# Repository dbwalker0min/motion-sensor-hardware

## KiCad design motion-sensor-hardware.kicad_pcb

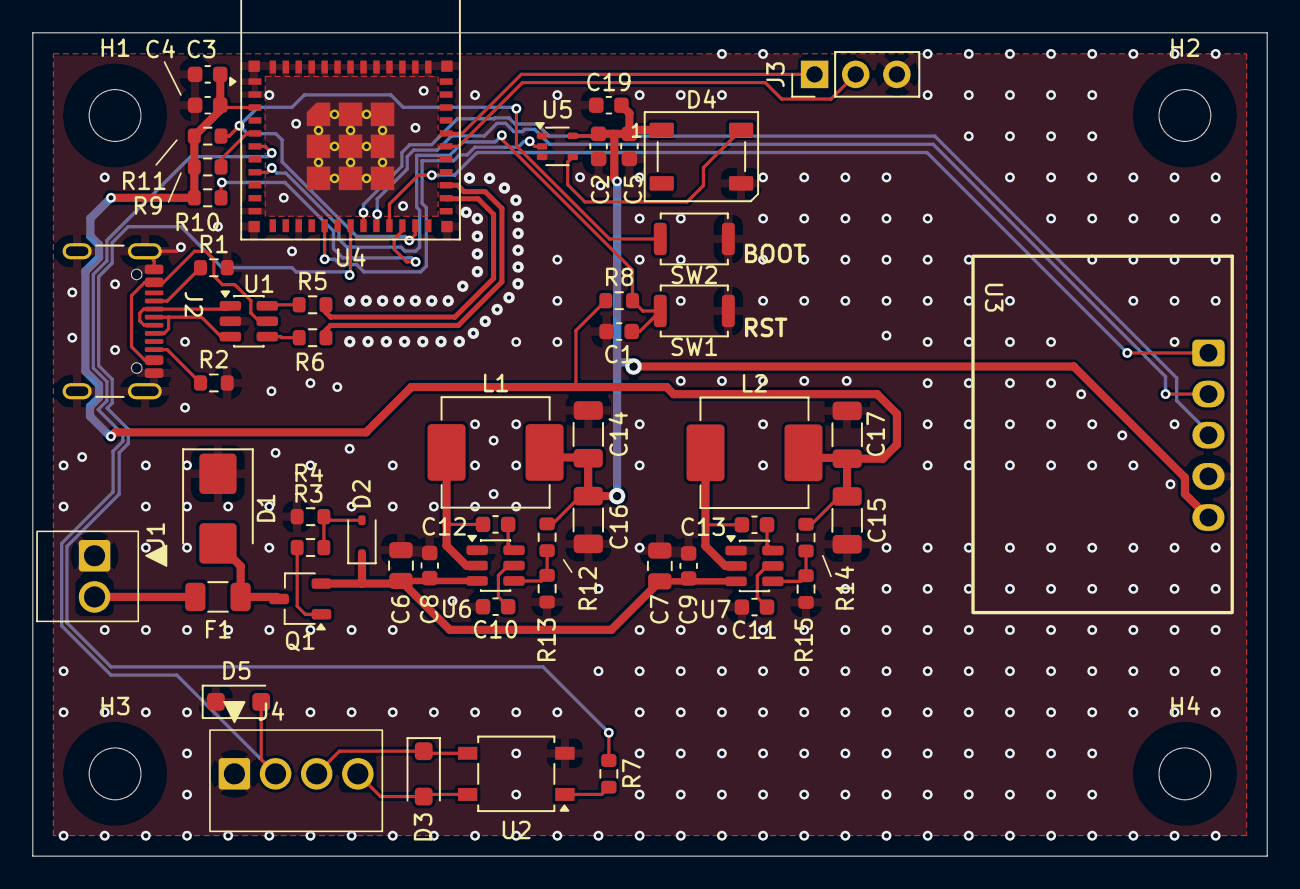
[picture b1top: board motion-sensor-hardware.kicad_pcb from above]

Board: 2 copper layers, 76.2 x 50.8 mm, 59 parts (0 on the bottom side), 41 nets.

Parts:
C1: 1uF; C_0603_1608Metric
C2, C3, C5, C8, C9, C10, C11, C12, C13: 100nF; C_0603_1608Metric
C4, C19: 10uF; C_0603_1608Metric
C6, C7: 10uF; C_0805_2012Metric
C14, C15, C16, C17: 47uF; C_1206_3216Metric
D1: SMBJ16CA; D_SMB
D2: BZT52C10S; D_SOD-323
D3, D5: SMF6.5CA; D_SOD-123F
D4: WS2812B-HS01/W; LED_WS2812B_PLCC4_5.0x5.0mm_P3.2mm
F1: JK-nSMD100/16V; Fuse_1206_3216Metric
H1, H2, H3, H4: MountingHole; MountingHole_3.2mm_M3
J1: MX128-2.54-02P
J2: TYPE-C 16PIN 2MD(073); USB_C_Receptacle_GCT_USB4105-xx-A_16P_TopMnt_Horizontal
J3: PZ254V-11-03P; PinHeader_1x03_P2.54mm_Vertical
J4: MX128-2.54-04P
L1, L2: FXL0630-6R8-M; L_Changjiang_FXL0630
Q1: AO3401A; TSOT-23
R1, R2: 5.1kΩ; R_0603_1608Metric
R3: 100Ω; R_0603_1608Metric
R4, R8, R9, R10, R11: 10kΩ; R_0603_1608Metric
R5, R6: 0Ω; R_0603_1608Metric
R7: 330Ω; R_0603_1608Metric
R12: 20kΩ; R_0603_1608Metric
R13: 3.6kΩ; R_0603_1608Metric
R14: 49.9kΩ; R_0603_1608Metric
R15: 15kΩ; R_0603_1608Metric
SW1, SW2: TS-1088-AR02016; SW_TS-1088-xx020xx_XUNPU
U1: USBLC6-2SC6; SOT-23-6
U2: ASSR-1218; SO-4_4.4x4.3mm_P2.54mm
U3: LD2410C
U4: ESP32-C3-MINI-1-N4; ESP32-C6-MINI-1
U5: SN74LV1T125DCK; SOT-353_SC-70-5
U6, U7: AP62200TWU-7; SOT-23-6

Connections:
+3.3V: C3.1, C4.1, C15.1, C17.1, L2.2, R8.1, R9.1, R10.1, R11.1, R14.1, U4.3 (3V3)
+5V: C2.1, C5.1, C14.1, C16.1, C19.1, D4.1 (VDD), L1.2, R12.1, U3.5 (VCC), U5.5 (VCC)
/CTL_SW1: D3.2 (A2), J4.4, U2.4
/CTL_SW2: D3.1 (A1), J4.3, U2.3
/LED: U4.16 (GPIO10), U5.2 (A)
/OUT: U3.3 (OUT), U4.19 (GPIO5/ADC2_CH0)
/RDR_RX: U3.2 (RX), U4.20 (GPIO6)
/RDR_TX: U3.1 (TX), U4.21 (GPIO7)
/STAT_SW: D5.2 (A2), J4.2, U4.6 (GPIO3/ADC1_CH3)
/SWON: R7.1, U4.18 (GPIO4/ADC1_CH4)
/UART_RXD: J3.2, U4.30 (GPIO20/U0RXD)
/UART_TXD: J3.1, U4.31 (GPIO21/U0TXD)
/USB+: R6.2, U4.27 (GPIO19/USB_D+)
/USB-: R5.2, U4.26 (GPIO18/USB_D-)
/VRAW: F1.1, J1.2
GND: C1.2, C2.2, C3.2, C4.2, C5.2, C6.2, C7.2, C8.2, C9.2, C10.2, C11.2, C14.2, C15.2, C16.2, C17.2, C19.2, D1.1 (A1), D4.3 (VSS), D5.1 (A1), J1.1, J2.A1 (GND), J2.A12 (GND), J2.B1 (GND), J2.B12 (GND), J2.S1 (SHIELD), J3.3, J4.1, R1.2, R2.2, R4.2, R13.2, R15.2, SW1.1, SW2.1, U1.2 (GND), U2.2, U3.4 (GND), U4.1 (GND), U4.2 (GND), U4.11 (GND), U4.14 (GND), U4.36 (GND), U4.37 (GND), U4.38 (GND), U4.39 (GND), U4.40 (GND), U4.41 (GND), U4.42 (GND), U4.43 (GND), U4.44 (GND), U4.45 (GND), U4.46 (GND), U4.47 (GND), U4.48 (GND), U4.49 (GND), U4.50 (GND), U4.51 (GND), U4.52 (GND), U4.53 (GND), U5.1 (~OE), U5.3 (GND), U6.1 (GND), U7.1 (GND)
unnamed: D1.2 (A2), F1.2, Q1.3 (D)
unnamed: D2.2 (A), R3.2, R4.1
unnamed: D4.4 (DIN), U5.4 (Y)
unnamed: J2.A5 (CC1), R1.1
unnamed: J2.B5 (CC2), R2.1
unnamed: J2.A6 (D+), J2.B6 (D+), U1.3 (I/O2)
unnamed: J2.A7 (D-), J2.B7 (D-), U1.1 (I/O1)
unnamed: Q1.1 (G), R3.1
unnamed: R5.1, U1.6 (I/O1)
unnamed: R6.1, U1.4 (I/O2)
unnamed: R7.2, U2.1
unnamed: J2.A4 (VBUS), J2.A9 (VBUS), J2.B4 (VBUS), J2.B9 (VBUS), U1.5 (VBUS)
unnamed: C1.1, R8.2, SW1.2, U4.8 (EN/CHIP_PU)
unnamed: R9.2, U4.5 (GPIO2/ADC1_CH2)
unnamed: R10.2, U4.22 (GPIO8)
unnamed: R11.2, SW2.2, U4.23 (GPIO9)
unnamed: C12.1, U6.6 (BST)
unnamed: C10.1, U6.5 (EN)
unnamed: R12.2, R13.1, U6.4 (FB)
unnamed: C12.2, L1.1, U6.2 (SW)
unnamed: C13.1, U7.6 (BST)
unnamed: C11.1, U7.5 (EN)
unnamed: R14.2, R15.1, U7.4 (FB)
unnamed: C13.2, L2.1, U7.2 (SW)
VIN: C6.1, C7.1, C8.1, C9.1, D2.1 (K), Q1.2 (S), U6.3 (VIN), U7.3 (VIN)

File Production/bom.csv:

Designator,Footprint,Quantity,Value,LCSC Part #
C1,0603,1,1uF,C15849
"C12, C13, C2, C3, C5, C8, C9",0603,7,100nF,C14663
"C14, C15, C16, C17",1206,4,47uF,C96123
"C19, C4",0603,2,10uF,C19702
"C6, C7",0805,2,10uF,C440198
D1,D_SMB,1,SMBJ16CA,C113990
D2,D_SOD-323,1,BZT52C10S,C19077446
"D3, D5",D_SOD-123F,2,SMF6.5CA,C19077501
D4,LED_WS2812B_PLCC4_5.0x5.0mm_P3.2mm,1,WS2812B-HS01/W,C22371521
F1,1206,1,JK-nSMD100/16V,C2830246
J1,MX128-2.54-02P,1,MX128-2.54-02P,C5188442
J2,USB_C_Receptacle_GCT_USB4105-xx-A_16P_TopMnt_Horizontal,1,TYPE-C 16PIN 2MD(073),C2765186
J4,MX128-2.54-04P,1,MX128-2.54-04P,C5188444
"L1, L2",L_Changjiang_FXL0630,2,FXL0630-6R8-M,C167221
Q1,TSOT-23,1,AO3401A,C15127
"R1, R2",0603,2,5.1kΩ,C23186
"R10, R11, R4, R8, R9",0603,5,10kΩ,C25804
R12,0603,1,20kΩ,C4184
R13,0603,1,3.6kΩ,C22980
R14,0603,1,49.9kΩ,C23184
R15,0603,1,15kΩ,C22809
R3,0603,1,100Ω,C22775
"R5, R6",0603,2,0Ω,C21189
R7,0603,1,330Ω,C23138
"SW1, SW2",SW_Push_SPST_NO_Alps_SKRK,2,TS-1088-AR02016,C720477
U1,SOT-23-6,1,USBLC6-2SC6,C7519
U2,SO-4_4.4x4.3mm_P2.54mm,1,ASSR-1218,C6747780
U3,LD2410C,1,LD2410C,C19723500
U4,ESP32-C6-MINI-1,1,ESP32-C3-MINI-1-N4,C2838502
U5,SOT-353_SC-70-5,1,SN74LV1T125DCK,C75925
"U6, U7",SOT-23-6,2,AP62200TWU-7,C2895288

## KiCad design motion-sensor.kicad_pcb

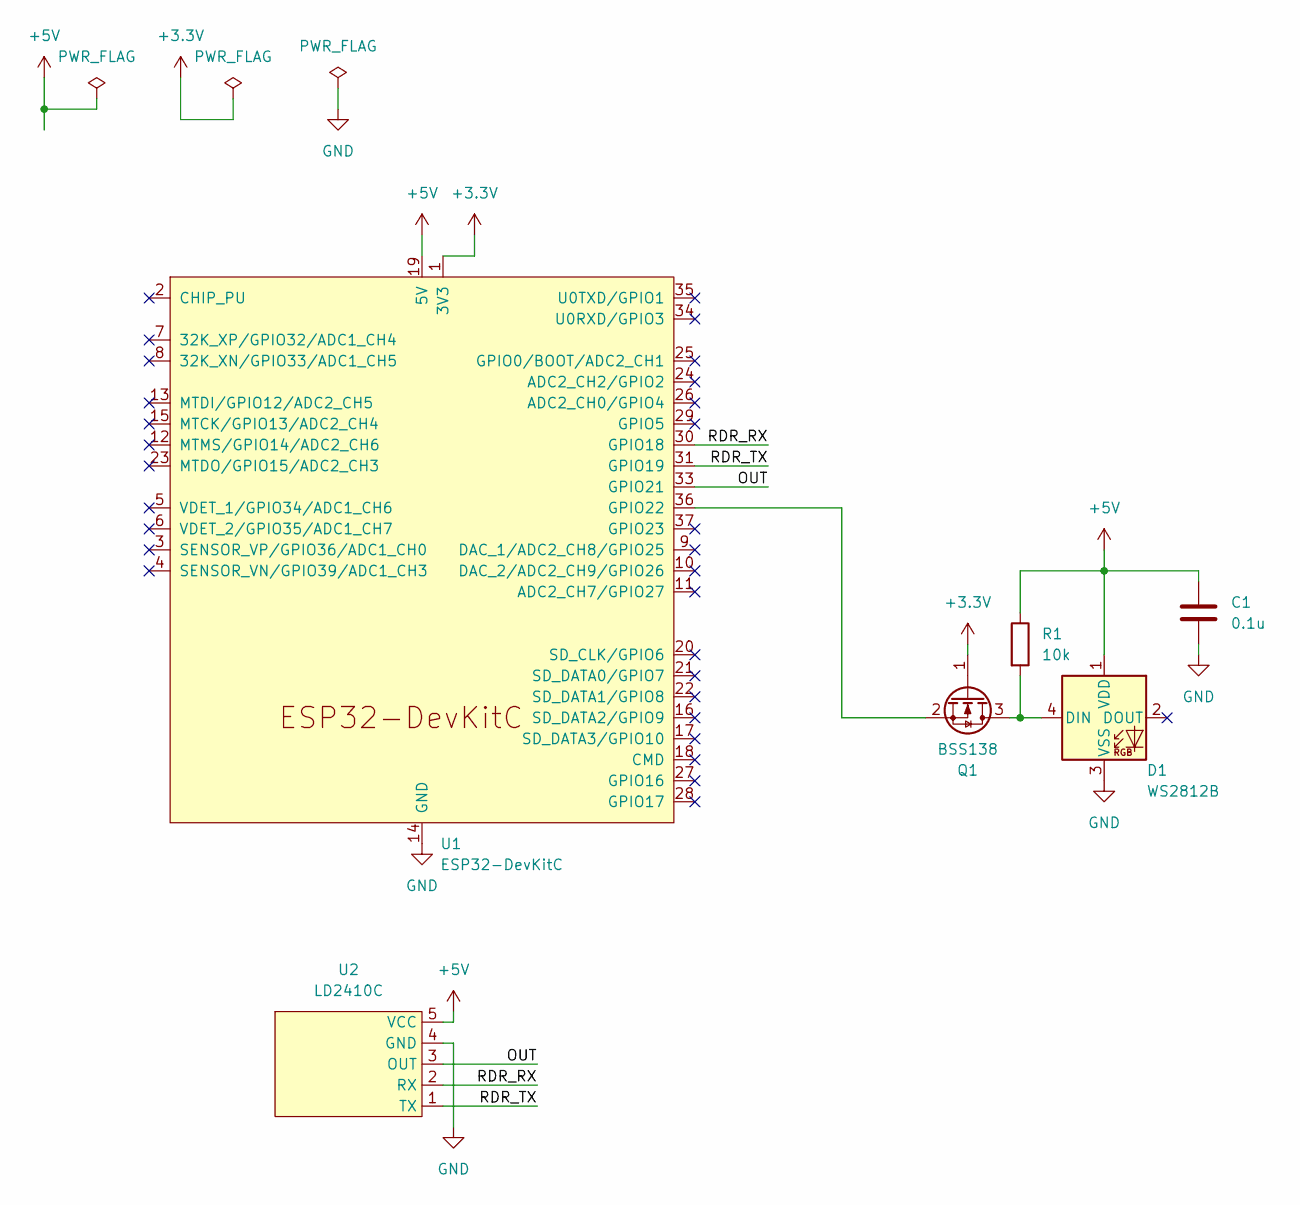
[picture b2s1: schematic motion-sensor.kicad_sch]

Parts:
C1: 0.1u; C_0805_2012Metric_Pad1.18x1.45mm_HandSolder
D1: WS2812B; LED_WS2812B_PLCC4_5.0x5.0mm_P3.2mm
Q1: BSS138; SOT-23
R1: 10k; R_0805_2012Metric_Pad1.20x1.40mm_HandSolder
U1: ESP32-DevKitC
U2: LD2410C

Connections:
+3.3V: Q1.1 (G), U1.1 (3V3)
+5V: C1.1, D1.1 (VDD), R1.1, U1.19 (5V), U2.5 (VCC)
/OUT: U1.33 (GPIO21), U2.3 (OUT)
/RX: U1.30 (GPIO18), U2.2 (RX)
/TX: U1.31 (GPIO19), U2.1 (TX)
GND: C1.2, D1.3 (VSS), U1.14 (GND), U1.32 (GND), U1.38 (GND), U2.4 (GND)
unnamed: D1.4 (DIN), Q1.3 (D), R1.2
unnamed: Q1.2 (S), U1.36 (GPIO22)

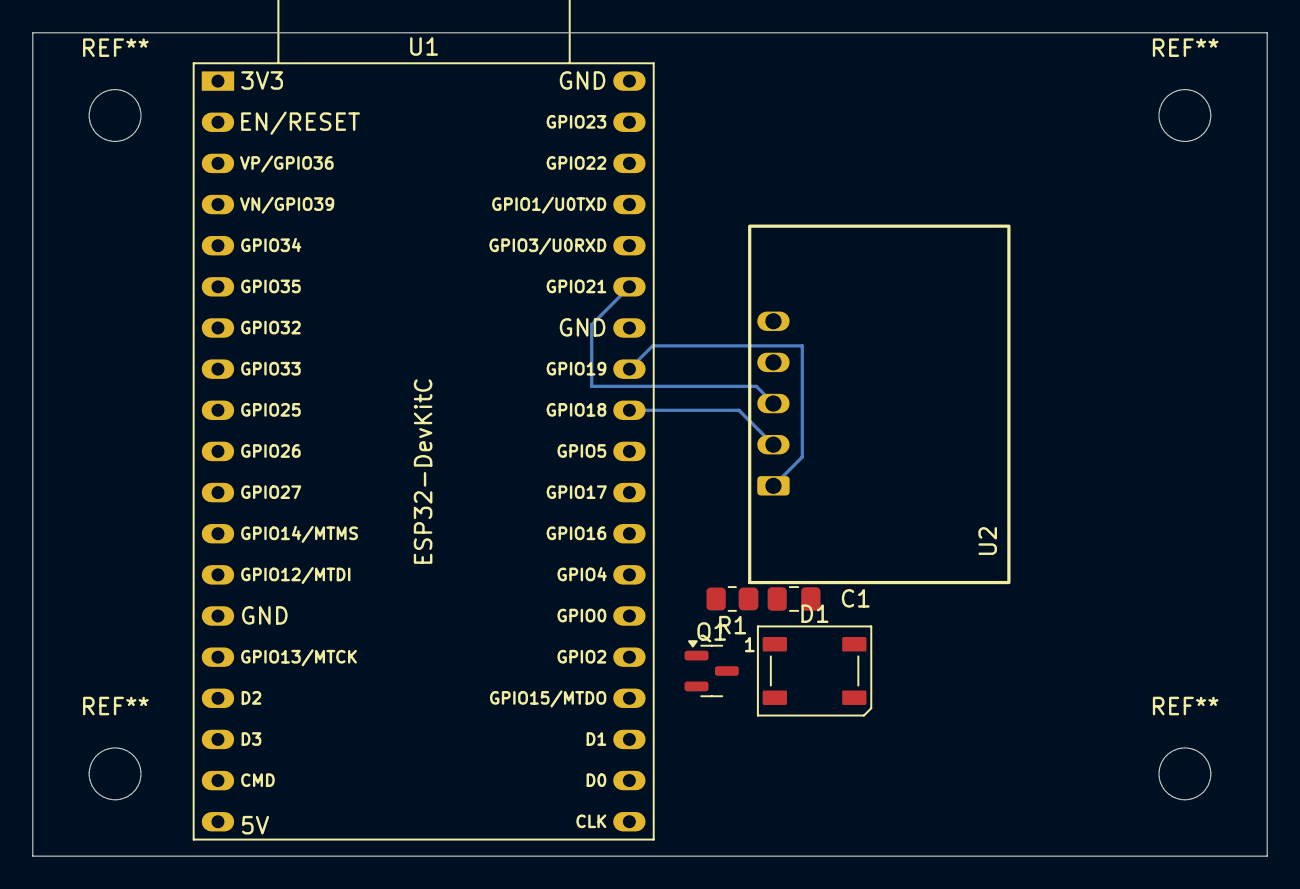
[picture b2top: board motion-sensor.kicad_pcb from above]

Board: 2 copper layers, 76.2 x 50.8 mm, 6 parts (0 on the bottom side), 8 nets.

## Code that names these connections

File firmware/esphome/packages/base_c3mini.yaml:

# Defaults (can be overridden by each device file)
substitutions:
  # These are the defined GPIO pins for Rev B
  pixel_pin: GPIO10
  radar_tx_pin: GPIO7
  radar_rx_pin: GPIO6
  radar_out_pin: GPIO5
  charger_status_pin: GPIO3
  charger_enable_pin: GPIO4
  
esp32:
  board: esp32-c3-devkitm-1
  variant: esp32c3
  framework:
    type: esp-idf

# Use defaults for these components
logger:
  level: DEBUG

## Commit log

2025-07-27 Deleted report.txt
2025-07-28 Generated artwork
2025-08-08 Switching converter for 12 V -> 5V. LDO for 5->3
2025-08-22 Added car charger circuits
2025-08-22 Added decoupling cap for LED and bigger cap for module
2025-08-28 Schematic relatively complete
2025-09-20 Updating regulator to use JLCPCB Basic part
2025-10-02 Ready to restart work!
2025-10-03 Schematic complete (I think)
2025-10-05 Split the two ground planes
2025-10-05 Rev B Submitted
2025-10-07 Got 3D export working
2025-10-09 Fixed screw term pin 1 issue
2025-10-16 Modified project structure
2025-10-16 Initial commit of motion sensor firmware
2025-10-16 Initial revision
2025-10-24 Added ld2410 sensor
2025-10-24 Got autocalibration working
